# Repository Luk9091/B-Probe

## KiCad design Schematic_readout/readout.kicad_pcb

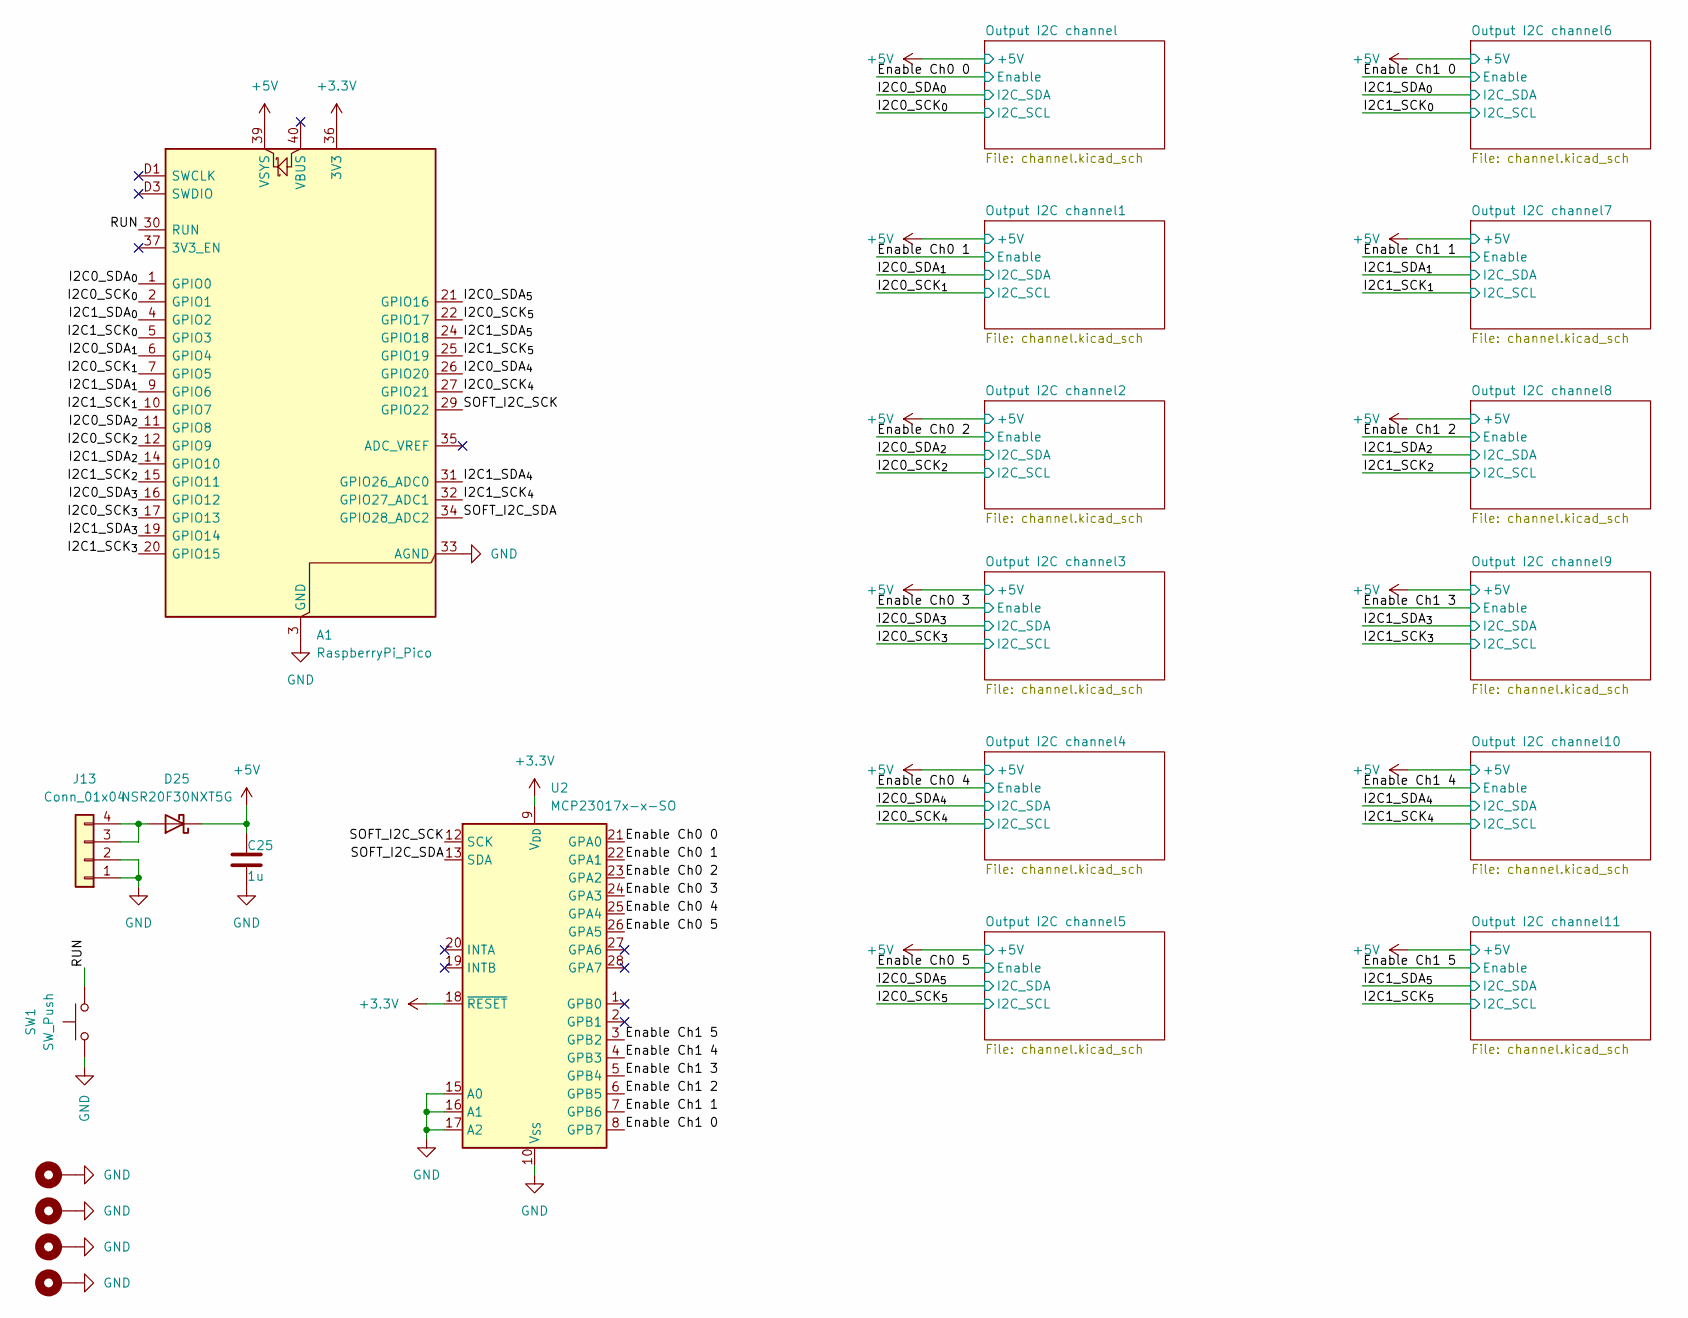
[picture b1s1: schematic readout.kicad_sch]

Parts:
A1: RaspberryPi_Pico; RaspberryPi_Pico_SMD_HandSolder
C25: 1u; C_0402_1005Metric
D25: NSR20F30NXT5G; D_0603_1608Metric
H1, H2, H3, H4: MountingHole_Pad; MountingHole_3.2mm_M3_Pad
J13: Conn_01x04; Molex_KK-254_AE-6410-04A_1x04_P2.54mm_Vertical
SW1: SW_Push; SW_SPST_TL3305B
U2: MCP23017x-x-SO; SOIC-28W_7.5x17.9mm_P1.27mm

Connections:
+3.3V: A1.36 (3V3), U2.9 (V_{DD}), U2.18 (~RESET); also elsewhere on the board
+5V: A1.39 (VSYS), C25.1, D25.1 (K); also elsewhere on the board
/Enable Ch0 0: U2.21 (GPA0); also elsewhere on the board
/Enable Ch0 1: U2.22 (GPA1); also elsewhere on the board
/Enable Ch0 2: U2.23 (GPA2); also elsewhere on the board
/Enable Ch0 3: U2.24 (GPA3); also elsewhere on the board
/Enable Ch0 4: U2.25 (GPA4); also elsewhere on the board
/Enable Ch0 5: U2.26 (GPA5); also elsewhere on the board
/Enable Ch1 0: U2.8 (GPB7); also elsewhere on the board
/Enable Ch1 1: U2.7 (GPB6); also elsewhere on the board
/Enable Ch1 2: U2.6 (GPB5); also elsewhere on the board
/Enable Ch1 3: U2.5 (GPB4); also elsewhere on the board
/Enable Ch1 4: U2.4 (GPB3); also elsewhere on the board
/Enable Ch1 5: U2.3 (GPB2); also elsewhere on the board
/I2C0_SCK_{0}: A1.2 (GPIO1); also elsewhere on the board
/I2C0_SCK_{1}: A1.7 (GPIO5); also elsewhere on the board
/I2C0_SCK_{2}: A1.12 (GPIO9); also elsewhere on the board
/I2C0_SCK_{3}: A1.17 (GPIO13); also elsewhere on the board
/I2C0_SCK_{4}: A1.27 (GPIO21); also elsewhere on the board
/I2C0_SCK_{5}: A1.22 (GPIO17); also elsewhere on the board
/I2C0_SDA_{0}: A1.1 (GPIO0); also elsewhere on the board
/I2C0_SDA_{1}: A1.6 (GPIO4); also elsewhere on the board
/I2C0_SDA_{2}: A1.11 (GPIO8); also elsewhere on the board
/I2C0_SDA_{3}: A1.16 (GPIO12); also elsewhere on the board
/I2C0_SDA_{4}: A1.26 (GPIO20); also elsewhere on the board
/I2C0_SDA_{5}: A1.21 (GPIO16); also elsewhere on the board
/I2C1_SCK_{0}: A1.5 (GPIO3); also elsewhere on the board
/I2C1_SCK_{1}: A1.10 (GPIO7); also elsewhere on the board
/I2C1_SCK_{2}: A1.15 (GPIO11); also elsewhere on the board
/I2C1_SCK_{3}: A1.20 (GPIO15); also elsewhere on the board
/I2C1_SCK_{4}: A1.32 (GPIO27_ADC1); also elsewhere on the board
/I2C1_SCK_{5}: A1.25 (GPIO19); also elsewhere on the board
/I2C1_SDA_{0}: A1.4 (GPIO2); also elsewhere on the board
/I2C1_SDA_{1}: A1.9 (GPIO6); also elsewhere on the board
/I2C1_SDA_{2}: A1.14 (GPIO10); also elsewhere on the board
/I2C1_SDA_{3}: A1.19 (GPIO14); also elsewhere on the board
/I2C1_SDA_{4}: A1.31 (GPIO26_ADC0); also elsewhere on the board
/I2C1_SDA_{5}: A1.24 (GPIO18); also elsewhere on the board
/RUN: A1.30 (RUN), SW1.1
/SOFT_I2C_SCK: A1.29 (GPIO22), U2.12 (SCK)
/SOFT_I2C_SDA: A1.34 (GPIO28_ADC2), U2.13 (SDA)
GND: A1.3 (GND), A1.8 (GND), A1.13 (GND), A1.18 (GND), A1.23 (GND), A1.28 (GND), A1.33 (AGND), A1.38 (GND), A1.D2 (GND), C25.2, H1.1 (1_1), H2.1 (1_1), H3.1 (1_1), H4.1 (1_1), J13.1, J13.2, SW1.2, U2.10 (V_{SS}), U2.15 (A0), U2.16 (A1), U2.17 (A2); also elsewhere on the board
unnamed: D25.2 (A), J13.3, J13.4

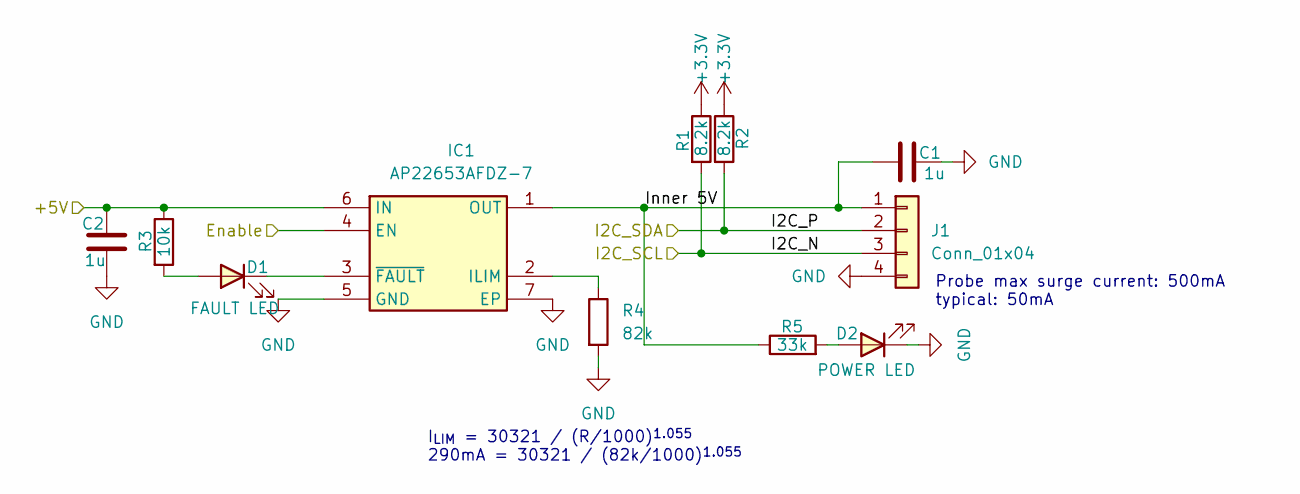
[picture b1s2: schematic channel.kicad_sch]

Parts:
C1, C2: 1u; C_0402_1005Metric
D1: FAULT LED; LED_0402_1005Metric
D2: POWER LED; LED_0402_1005Metric
IC1: AP22653AFDZ-7; SON65P200X200X80-7N; Mouser Part Number 621-AP22653AFDZ-7
J1: Conn_01x04; Molex_KK-254_AE-6410-04A_1x04_P2.54mm_Vertical
R1, R2: 8.2k; R_0402_1005Metric
R3: 10k; R_0402_1005Metric
R4: 82k; R_0402_1005Metric
R5: 33k; R_0402_1005Metric

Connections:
+3.3V: R1.1, R2.1; also elsewhere on the board
+5V: C2.1, IC1.6 (IN), R3.1; also elsewhere on the board
/Enable Ch0 0: IC1.4 (EN); also elsewhere on the board
/I2C0_SCK_{0}: J1.3, R1.2; also elsewhere on the board
/I2C0_SDA_{0}: J1.2, R2.2; also elsewhere on the board
/Output I2C channel/Inner 5V: C1.2, IC1.1 (OUT), J1.1, R5.1
GND: C1.1, C2.2, D2.1 (K), IC1.5 (GND), IC1.7 (EP), J1.4, R4.2; also elsewhere on the board
unnamed: D1.2 (A), R3.2
unnamed: D1.1 (K), IC1.3 (~FAULT)
unnamed: D2.2 (A), R5.2
unnamed: IC1.2 (ILIM), R4.1

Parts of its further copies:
C3, C4, C5, C6, C7, C8, C9, C10, C11, C12, C13, C14, C15, C16, C17, C18, C19, C20, C21, C22, C23, C24: 1u; C_0402_1005Metric
D3, D5, D7, D9, D11, D13, D15, D17, D19, D21, D23: FAULT LED; LED_0402_1005Metric
D4, D6, D8, D10, D12, D14, D16, D18, D20, D22, D24: POWER LED; LED_0402_1005Metric
IC2, IC3, IC4, IC5, IC6, IC7, IC8, IC9, IC10, IC11, IC12: AP22653AFDZ-7; SON65P200X200X80-7N; Mouser Part Number 621-AP22653AFDZ-7
J2, J3, J4, J5, J6, J7, J8, J9, J10, J11, J12: Conn_01x04; Molex_KK-254_AE-6410-04A_1x04_P2.54mm_Vertical
R6, R7, R11, R12, R16, R17, R21, R22, R26, R27, R31, R32, R36, R37, R41, R42, R46, R47, R51, R52, R56, R57: 8.2k; R_0402_1005Metric
R8, R13, R18, R23, R28, R33, R38, R43, R48, R53, R58: 10k; R_0402_1005Metric
R9, R14, R19, R24, R29, R34, R39, R44, R49, R54, R59: 82k; R_0402_1005Metric
R10, R15, R20, R25, R30, R35, R40, R45, R50, R55, R60: 33k; R_0402_1005Metric

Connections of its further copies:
+3.3V: R6.1, R7.1, R11.1, R12.1, R16.1, R17.1, R21.1, R22.1, R26.1, R27.1, R31.1, R32.1, R36.1, R37.1, R41.1, R42.1, R46.1, R47.1, R51.1, R52.1, R56.1, R57.1; also elsewhere on the board
+5V: C4.1, C6.1, C8.1, C10.1, C12.1, C14.1, C16.1, C18.1, C20.1, C22.1, C24.1, IC2.6 (IN), IC3.6 (IN), IC4.6 (IN), IC5.6 (IN), IC6.6 (IN), IC7.6 (IN), IC8.6 (IN), IC9.6 (IN), IC10.6 (IN), IC11.6 (IN), IC12.6 (IN), R8.1, R13.1, R18.1, R23.1, R28.1, R33.1, R38.1, R43.1, R48.1, R53.1, R58.1; also elsewhere on the board
/Enable Ch0 1: IC2.4 (EN); also elsewhere on the board
/Enable Ch0 2: IC3.4 (EN); also elsewhere on the board
/Enable Ch0 3: IC4.4 (EN); also elsewhere on the board
/Enable Ch0 4: IC5.4 (EN); also elsewhere on the board
/Enable Ch0 5: IC6.4 (EN); also elsewhere on the board
/Enable Ch1 0: IC7.4 (EN); also elsewhere on the board
/Enable Ch1 1: IC8.4 (EN); also elsewhere on the board
/Enable Ch1 2: IC9.4 (EN); also elsewhere on the board
/Enable Ch1 3: IC10.4 (EN); also elsewhere on the board
/Enable Ch1 4: IC11.4 (EN); also elsewhere on the board
/Enable Ch1 5: IC12.4 (EN); also elsewhere on the board
/I2C0_SCK_{1}: J2.3, R6.2; also elsewhere on the board
/I2C0_SCK_{2}: J3.3, R11.2; also elsewhere on the board
/I2C0_SCK_{3}: J4.3, R16.2; also elsewhere on the board
/I2C0_SCK_{4}: J5.3, R21.2; also elsewhere on the board
/I2C0_SCK_{5}: J6.3, R26.2; also elsewhere on the board
/I2C0_SDA_{1}: J2.2, R7.2; also elsewhere on the board
/I2C0_SDA_{2}: J3.2, R12.2; also elsewhere on the board
/I2C0_SDA_{3}: J4.2, R17.2; also elsewhere on the board
/I2C0_SDA_{4}: J5.2, R22.2; also elsewhere on the board
/I2C0_SDA_{5}: J6.2, R27.2; also elsewhere on the board
/I2C1_SCK_{0}: J7.3, R31.2; also elsewhere on the board
/I2C1_SCK_{1}: J8.3, R36.2; also elsewhere on the board
/I2C1_SCK_{2}: J9.3, R41.2; also elsewhere on the board
/I2C1_SCK_{3}: J10.3, R46.2; also elsewhere on the board
/I2C1_SCK_{4}: J11.3, R51.2; also elsewhere on the board
/I2C1_SCK_{5}: J12.3, R56.2; also elsewhere on the board
/I2C1_SDA_{0}: J7.2, R32.2; also elsewhere on the board
/I2C1_SDA_{1}: J8.2, R37.2; also elsewhere on the board
/I2C1_SDA_{2}: J9.2, R42.2; also elsewhere on the board
/I2C1_SDA_{3}: J10.2, R47.2; also elsewhere on the board
/I2C1_SDA_{4}: J11.2, R52.2; also elsewhere on the board
/I2C1_SDA_{5}: J12.2, R57.2; also elsewhere on the board
/Output I2C channel1/Inner 5V: C3.2, IC2.1 (OUT), J2.1, R10.1
/Output I2C channel2/Inner 5V: C5.2, IC3.1 (OUT), J3.1, R15.1
/Output I2C channel3/Inner 5V: C7.2, IC4.1 (OUT), J4.1, R20.1
/Output I2C channel4/Inner 5V: C9.2, IC5.1 (OUT), J5.1, R25.1
/Output I2C channel5/Inner 5V: C11.2, IC6.1 (OUT), J6.1, R30.1
/Output I2C channel6/Inner 5V: C13.2, IC7.1 (OUT), J7.1, R35.1
/Output I2C channel7/Inner 5V: C15.2, IC8.1 (OUT), J8.1, R40.1
/Output I2C channel8/Inner 5V: C17.2, IC9.1 (OUT), J9.1, R45.1
/Output I2C channel9/Inner 5V: C19.2, IC10.1 (OUT), J10.1, R50.1
/Output I2C channel10/Inner 5V: C21.2, IC11.1 (OUT), J11.1, R55.1
/Output I2C channel11/Inner 5V: C23.2, IC12.1 (OUT), J12.1, R60.1
GND: C3.1, C4.2, C5.1, C6.2, C7.1, C8.2, C9.1, C10.2, C11.1, C12.2, C13.1, C14.2, C15.1, C16.2, C17.1, C18.2, C19.1, C20.2, C21.1, C22.2, C23.1, C24.2, D4.1 (K), D6.1 (K), D8.1 (K), D10.1 (K), D12.1 (K), D14.1 (K), D16.1 (K), D18.1 (K), D20.1 (K), D22.1 (K), D24.1 (K), IC2.5 (GND), IC2.7 (EP), IC3.5 (GND), IC3.7 (EP), IC4.5 (GND), IC4.7 (EP), IC5.5 (GND), IC5.7 (EP), IC6.5 (GND), IC6.7 (EP), IC7.5 (GND), IC7.7 (EP), IC8.5 (GND), IC8.7 (EP), IC9.5 (GND), IC9.7 (EP), IC10.5 (GND), IC10.7 (EP), IC11.5 (GND), IC11.7 (EP), IC12.5 (GND), IC12.7 (EP), J2.4, J3.4, J4.4, J5.4, J6.4, J7.4, J8.4, J9.4, J10.4, J11.4, J12.4, R9.2, R14.2, R19.2, R24.2, R29.2, R34.2, R39.2, R44.2, R49.2, R54.2, R59.2; also elsewhere on the board
unnamed: D3.2 (A), R8.2
unnamed: D3.1 (K), IC2.3 (~FAULT)
unnamed: D4.2 (A), R10.2
unnamed: D5.2 (A), R13.2
unnamed: D5.1 (K), IC3.3 (~FAULT)
unnamed: D6.2 (A), R15.2
unnamed: D7.2 (A), R18.2
unnamed: D7.1 (K), IC4.3 (~FAULT)
unnamed: D8.2 (A), R20.2
unnamed: D9.2 (A), R23.2
unnamed: D9.1 (K), IC5.3 (~FAULT)
unnamed: D10.2 (A), R25.2
unnamed: D11.2 (A), R28.2
unnamed: D11.1 (K), IC6.3 (~FAULT)
unnamed: D12.2 (A), R30.2
unnamed: D13.2 (A), R33.2
unnamed: D13.1 (K), IC7.3 (~FAULT)
unnamed: D14.2 (A), R35.2
unnamed: D15.2 (A), R38.2
unnamed: D15.1 (K), IC8.3 (~FAULT)
unnamed: D16.2 (A), R40.2
unnamed: D17.2 (A), R43.2
unnamed: D17.1 (K), IC9.3 (~FAULT)
unnamed: D18.2 (A), R45.2
unnamed: D19.2 (A), R48.2
unnamed: D19.1 (K), IC10.3 (~FAULT)
unnamed: D20.2 (A), R50.2
unnamed: D21.2 (A), R53.2
unnamed: D21.1 (K), IC11.3 (~FAULT)
unnamed: D22.2 (A), R55.2
unnamed: D23.2 (A), R58.2
unnamed: D23.1 (K), IC12.3 (~FAULT)
unnamed: D24.2 (A), R60.2
unnamed: IC2.2 (ILIM), R9.1
unnamed: IC3.2 (ILIM), R14.1
unnamed: IC4.2 (ILIM), R19.1
unnamed: IC5.2 (ILIM), R24.1
unnamed: IC6.2 (ILIM), R29.1
unnamed: IC7.2 (ILIM), R34.1
unnamed: IC8.2 (ILIM), R39.1
unnamed: IC9.2 (ILIM), R44.1
unnamed: IC10.2 (ILIM), R49.1
unnamed: IC11.2 (ILIM), R54.1
unnamed: IC12.2 (ILIM), R59.1

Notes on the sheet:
Probe max surge current: 500mA typical: 50mA
I_{LIM} = 30321 / (R/1000)^{1.055} 290mA = 30321 / (82k/1000)^{1.055}

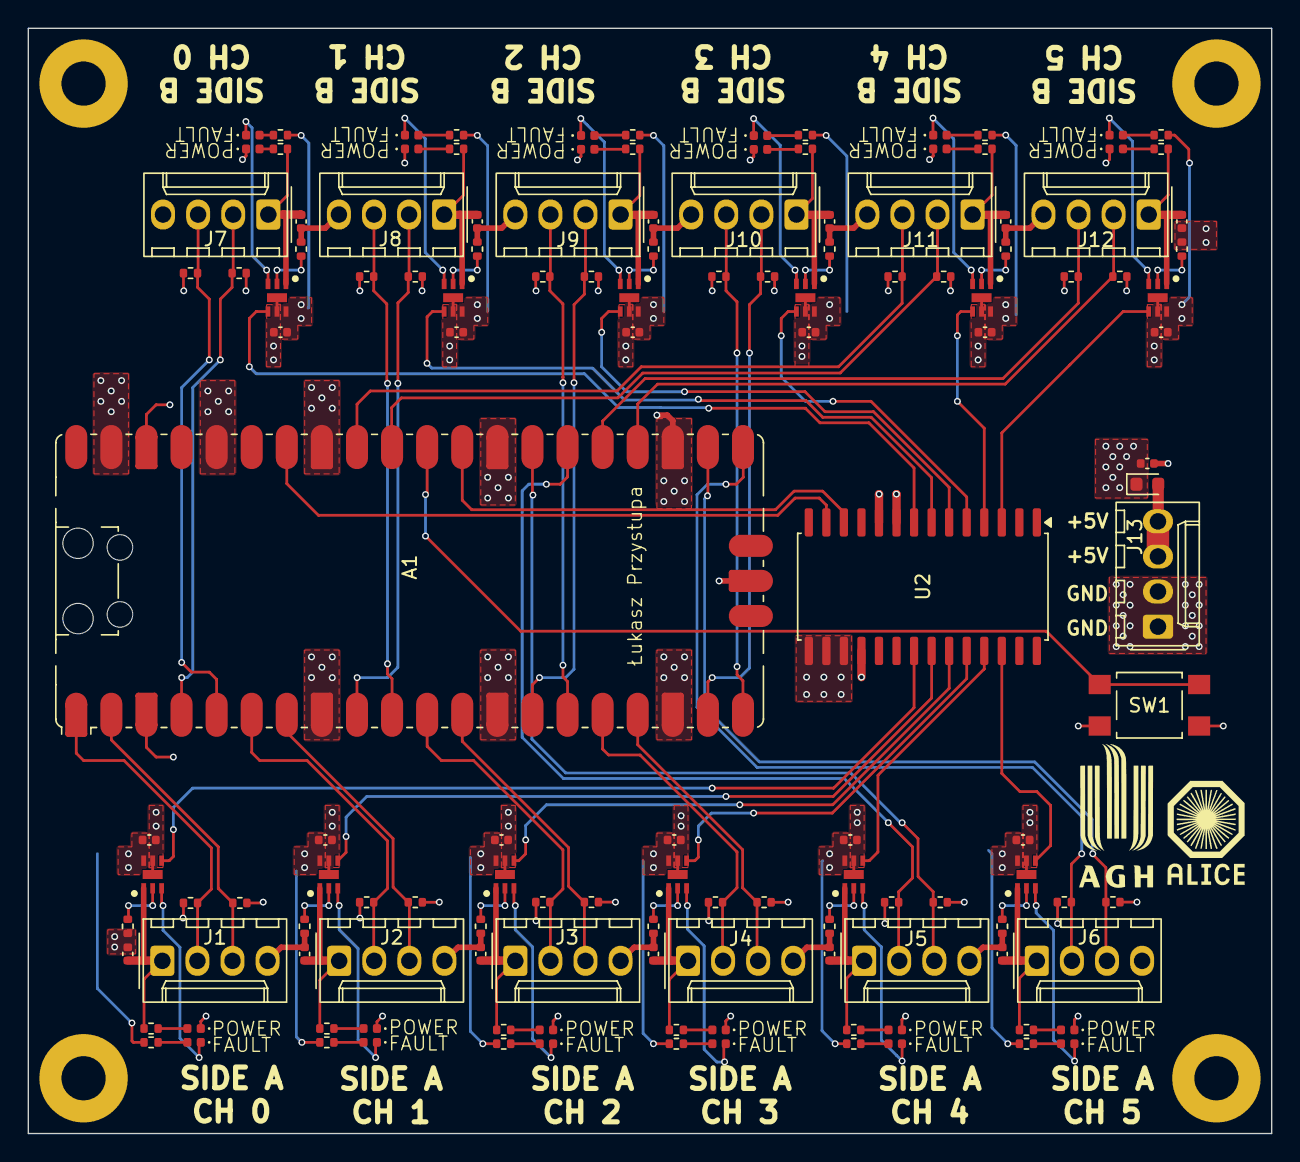
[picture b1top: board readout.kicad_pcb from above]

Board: 4 copper layers, 90.0 x 80.0 mm, 142 parts (0 on the bottom side), 103 nets.

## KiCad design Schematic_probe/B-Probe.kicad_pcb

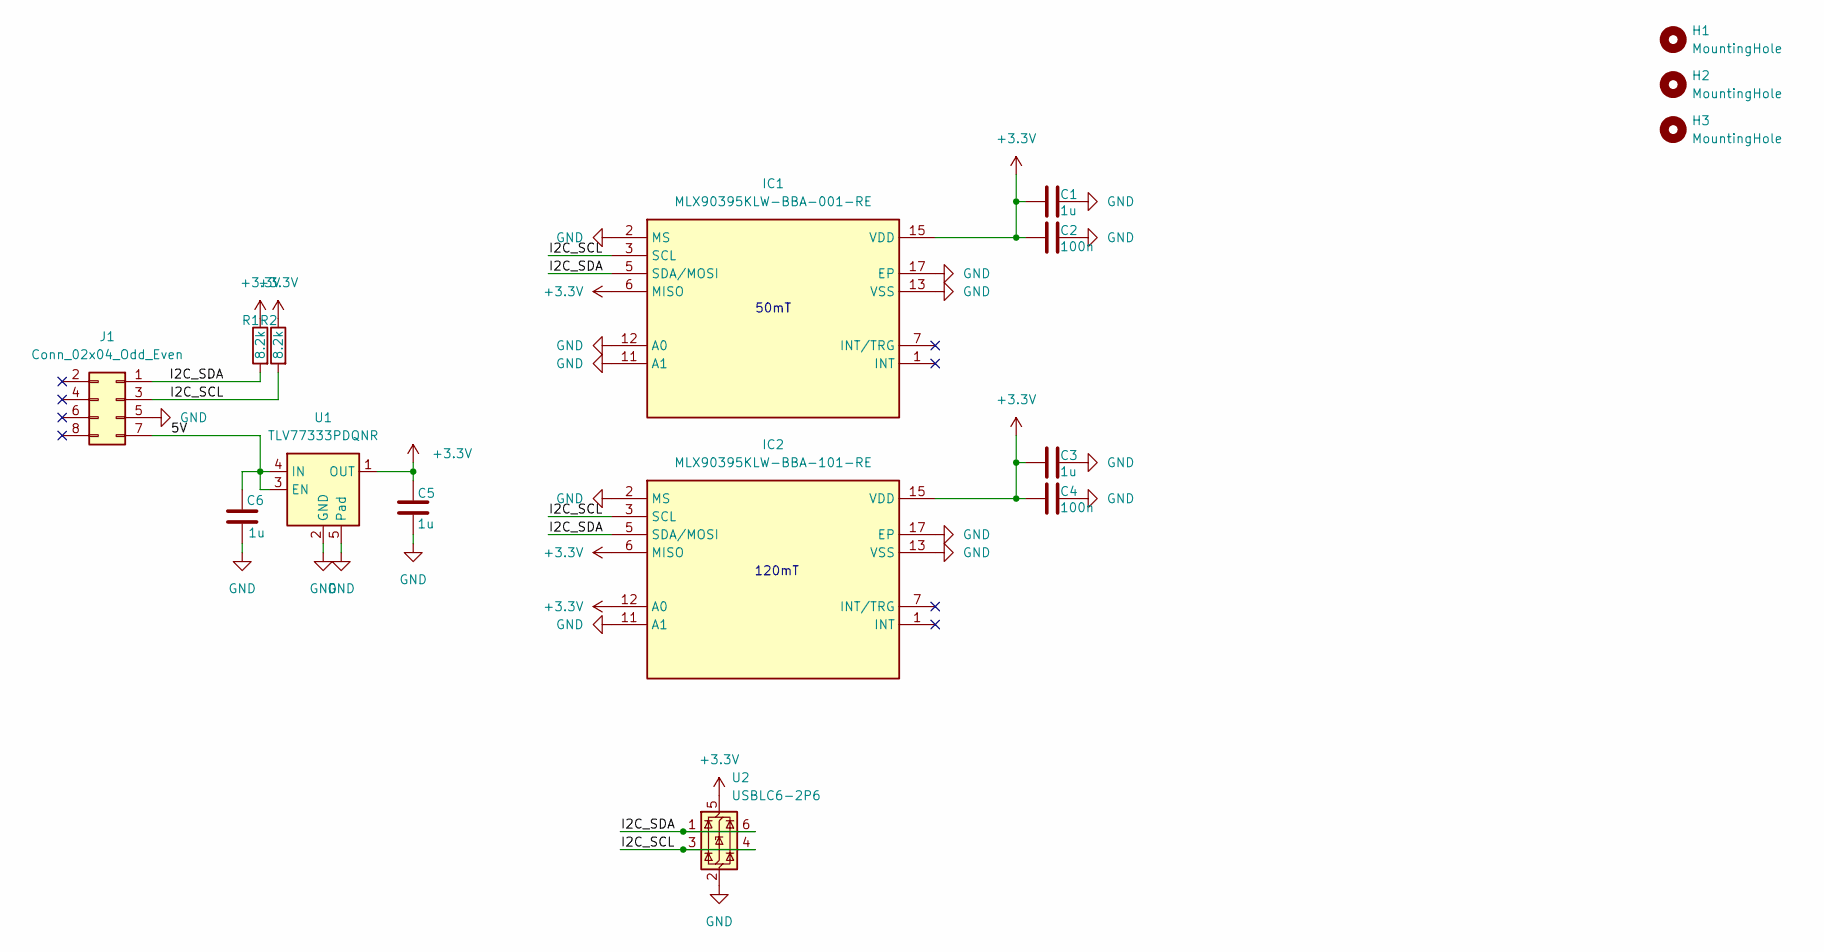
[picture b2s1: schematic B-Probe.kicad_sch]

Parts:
C1, C3, C5, C6: 1u; C_0201_0603Metric
C2, C4: 100n; C_0201_0603Metric
H1, H2, H3: MountingHole; MountingHole_2.2mm_M2
IC1: MLX90395KLW-BBA-001-RE; QFN50P300X300X100-17N-D; Mouser Part Number 482-90395KLWBBA001RE
IC2: MLX90395KLW-BBA-101-RE; QFN50P300X300X100-17N-D; Mouser Part Number 482-90395KLWBBA101RE
J1: Conn_02x04_Odd_Even; PinHeader_2x04_P1.27mm_Vertical
R1, R2: 8.2k; R_0201_0603Metric
U1: TLV77333PDQNR; Texas_X2SON-4_1x1mm_P0.65mm
U2: USBLC6-2P6; SOT-666

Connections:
+3.3V: C1.1, C2.1, C3.1, C4.1, C5.1, IC1.6 (MISO), IC1.15 (VDD), IC2.6 (MISO), IC2.12 (A0), IC2.15 (VDD), R1.1, R2.1, U1.1 (OUT), U2.5 (VBUS)
/5V: C6.1, J1.7, U1.3 (EN), U1.4 (IN)
/I2C_SCL: IC1.3 (SCL), IC2.3 (SCL), J1.3, R2.2, U2.3 (I/O2), U2.4 (I/O2)
/I2C_SDA: IC1.5 (SDA/MOSI), IC2.5 (SDA/MOSI), J1.1, R1.2, U2.1 (I/O1), U2.6 (I/O1)
GND: C1.2, C2.2, C3.2, C4.2, C5.2, C6.2, IC1.2 (MS), IC1.4 (NOT_USED_1), IC1.8 (NOT_USED_3), IC1.9 (NOT_USED_4), IC1.10 (NOT_USED_5), IC1.11 (A1), IC1.12 (A0), IC1.13 (VSS), IC1.14 (NOT_USED_6), IC1.16 (NOT_USED_7), IC1.17 (EP), IC2.2 (MS), IC2.4 (NOT_USED_1), IC2.8 (NOT_USED_3), IC2.9 (NOT_USED_4), IC2.10 (NOT_USED_5), IC2.11 (A1), IC2.13 (VSS), IC2.14 (NOT_USED_6), IC2.16 (NOT_USED_7), IC2.17 (EP), J1.5, U1.2 (GND), U1.5 (Pad), U2.2 (GND)

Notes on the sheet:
120mT
50mT

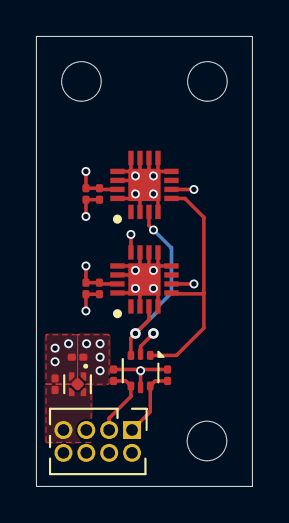
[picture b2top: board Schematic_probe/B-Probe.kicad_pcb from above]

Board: 4 copper layers, 12.0 x 25.0 mm, 16 parts (0 on the bottom side), 5 nets.

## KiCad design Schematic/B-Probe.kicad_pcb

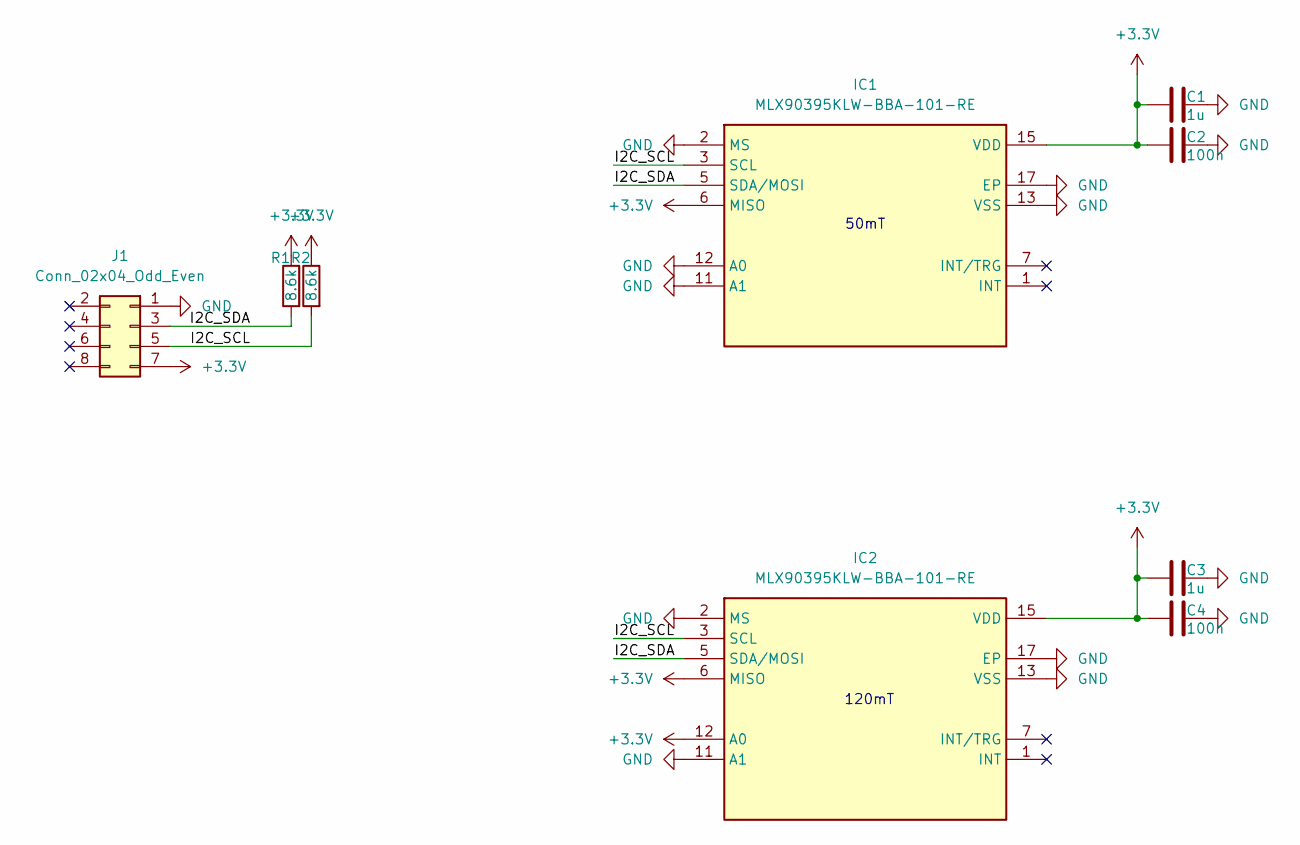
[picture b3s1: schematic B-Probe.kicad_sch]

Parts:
C1, C3: 1u; C_0201_0603Metric
C2, C4: 100n; C_0201_0603Metric
IC1, IC2: MLX90395KLW-BBA-101-RE; QFN50P300X300X100-17N-D; Mouser Part Number 482-90395KLWBBA101RE
J1: Conn_02x04_Odd_Even; PinHeader_2x04_P1.00mm_Vertical
R1, R2: 8.6k; R_0201_0603Metric

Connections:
+3.3V: C1.1, C2.1, C3.1, C4.1, IC1.6 (MISO), IC1.15 (VDD), IC2.6 (MISO), IC2.12 (A0), IC2.15 (VDD), J1.7, R1.1, R2.1
/I2C_SCL: IC1.3 (SCL), IC2.3 (SCL), J1.5, R2.2
/I2C_SDA: IC1.5 (SDA/MOSI), IC2.5 (SDA/MOSI), J1.3, R1.2
GND: C1.2, C2.2, C3.2, C4.2, IC1.2 (MS), IC1.4 (NOT_USED_1), IC1.8 (NOT_USED_3), IC1.9 (NOT_USED_4), IC1.10 (NOT_USED_5), IC1.11 (A1), IC1.12 (A0), IC1.13 (VSS), IC1.14 (NOT_USED_6), IC1.16 (NOT_USED_7), IC1.17 (EP), IC2.2 (MS), IC2.4 (NOT_USED_1), IC2.8 (NOT_USED_3), IC2.9 (NOT_USED_4), IC2.10 (NOT_USED_5), IC2.11 (A1), IC2.13 (VSS), IC2.14 (NOT_USED_6), IC2.16 (NOT_USED_7), IC2.17 (EP), J1.1

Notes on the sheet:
120mT
50mT

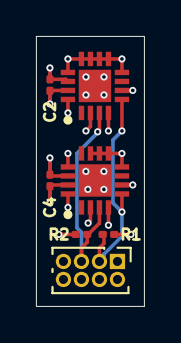
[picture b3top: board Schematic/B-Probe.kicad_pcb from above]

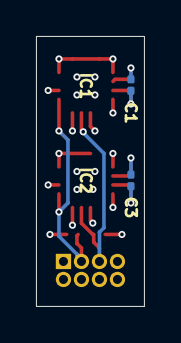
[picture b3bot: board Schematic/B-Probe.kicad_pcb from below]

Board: 4 copper layers, 6.0 x 15.0 mm, 9 parts (2 on the bottom side), 4 nets.
